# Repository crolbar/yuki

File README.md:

<h1 align="center">YUKI</h1>

<div align="center">
YUKI is a split diodless keyboard with a column stagger layout heavily inspired by <a href="https://github.com/diepala/cantor">cantor</a>.
</div>
<br/><br/>

Made with [Keyberon](https://github.com/TeXitoi/keyberon)

<br/>

### Layers
| Layer                                                                                      | Description              |
|--------------------------------------------------------------------------------------------|--------------------------|
| [Layer 0](https://www.keyboard-layout-editor.com/#/gists/67aaf9d778e9b2ddf6e25b263cbe5ed5) | Firmware Dvorak          |
| [Layer 1](https://www.keyboard-layout-editor.com/#/gists/5f7a4db98ea4d0b959304c4fe80d1d7f) | Numbers & Symbols        |
| [Layer 2](https://www.keyboard-layout-editor.com/#/gists/3af9d73abaec154f56b99b5a6c55cf5e) | Less used keys & Macros  |
| [Layer 3](https://www.keyboard-layout-editor.com/#/gists/ff861bef767ebb767786974deb496a8b) | Mouse movement & buttons |
| [Layer 4](https://www.keyboard-layout-editor.com/#/gists/a4c8d92eb2a6d883765b2eac82c46641) | Qwerty                   |

<br/>

### Features

- 44 keys, v0.1 - Cherry MX & v0.2 - Kailh Choc V1 switches
- Uses only 1U keycaps
- TRRS connection is used for communication between the two halves
- 2 USB-C connectors, with a choice from which the keyboard should send keystrokes
- Mouse control
- OLED display (not installed in the v0.2 picture)

<br/>

# Bill of Materials

| Product       | Qty | Note                                                                                                                                                                                                        |
|---------------|-----|-------------------------------------------------------------------------------------------------------------------------------------------------------------------------------------------------------------|
| YUKI PCB      | 2   | [KiCad](https://kicad.org/) project files can be found in `yuki_pcb` directory. I ordered them from [JLCPCB](https://jlcpcb.com). They are reversible so you will use the same pcb for both left and right. |
| STM32F401CCU6 | 2   | Can be found on aliexpress. I have ordered mine from a local vendor.                                                                                                                                        |
| TRRS jacks    | 2   | `PJ-320A`                                                                                                                                                                                                   |
| TRRS cable    | 1   | 3.5mm jack cable, with 3 stripes.                                                                                                                                                                           |
| Switches      | 44  | Cherry MX for v0.1 and Kailh Choc V1 for v0.2. Ordered from [splitkb](https://splitkb.com/collections/switches-and-keycaps/products/kailh-low-profile-choc-switches)                                        |
| Keycaps       | 44  | 1U keycaps. Ordered from [splitkb](https://splitkb.com/collections/switches-and-keycaps/products/blank-mbk-choc-low-profile-keycaps).                                                                       |

# Flashing the firmware

You will need rust installed so:
```
curl --proto '=https' --tlsv1.2 -sSf https://sh.rustup.rs | sh
```

cargo-binutils for stripping unused data from the rust binary and other optimizations:
```
rustup component add llvm-tools
cargo install cargo-binutils
```

dfu-util for flashing:
```
sudo pacman -S dfu-util
```

add the rust target for the MCU:
```
rustup target add thumbv7em-none-eabihf
```

then to compile the firmware:
``` 
cargo objcopy --bin yuki --release -- -O binary yuki.bin
```
for the right board add `--features right`

to flash enter dfu by holding BOOT clicking RESET and releasing BOOT and enter (can be tricky):
```
dfu-util -d 0483:df11 -a 0 --dfuse-address 0x08000000:leave -D yuki.bin"
```

After that to enter dfu just hold button 05 and 33 click reset and release the buttons.

### Nix

if you are on NixOS you could use the devShell:

enter the dev shell:
```
nix develop
```

and use the flash script that can be found in `flash.nix`
```
flash right
```

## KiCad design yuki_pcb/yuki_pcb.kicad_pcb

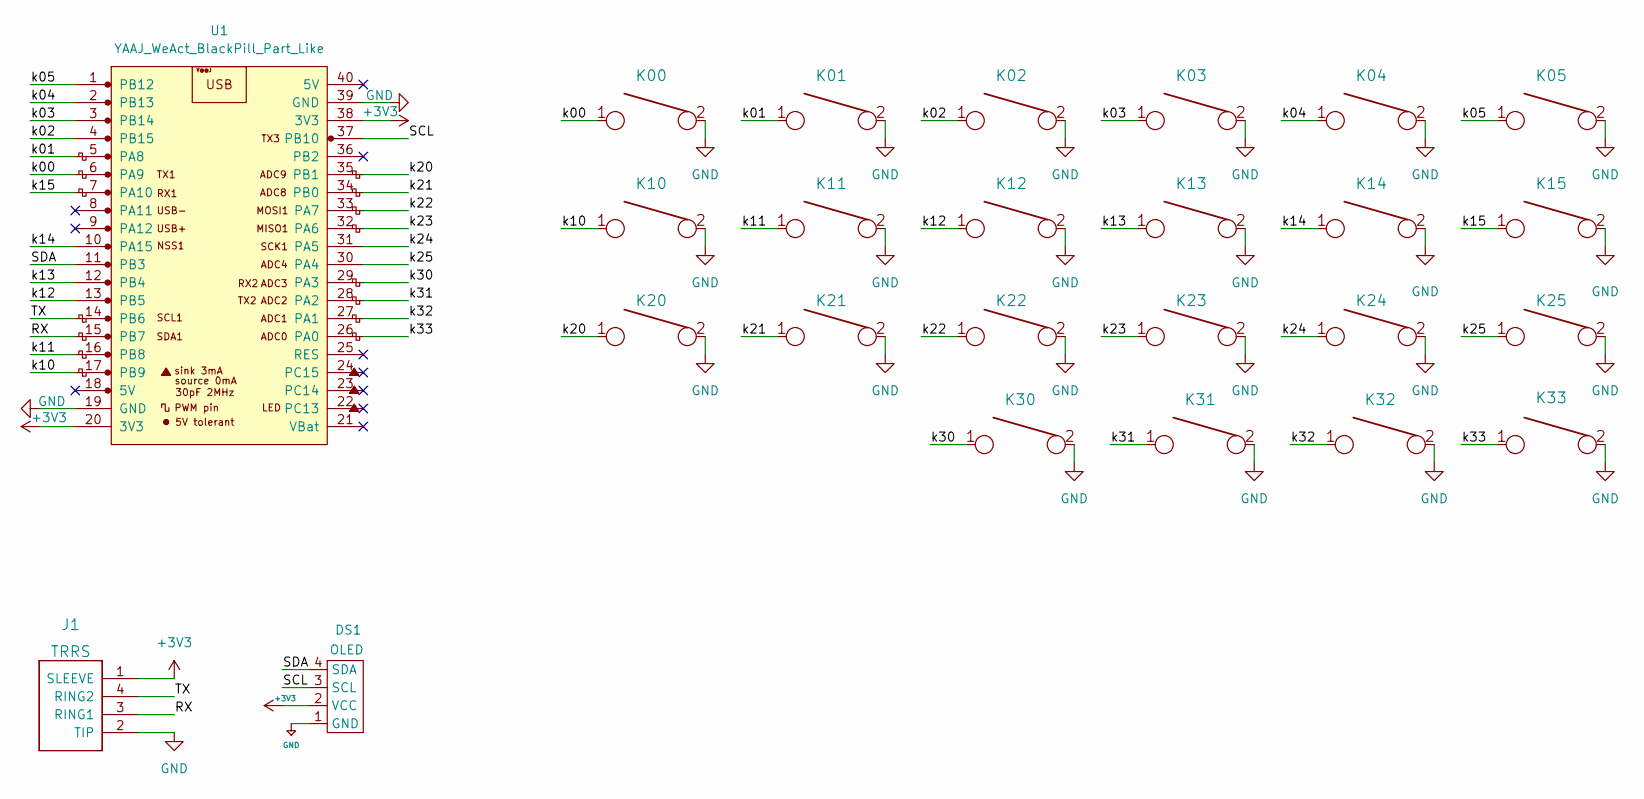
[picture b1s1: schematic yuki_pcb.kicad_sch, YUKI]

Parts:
DS1: OLED
J1: TRRS; MJ-4PP-9_Cantor_MX_TX-RX_Crossover
K00, K01, K02, K03, K04, K05, K10, K11, K12, K13, K14, K15, K20, K21, K22, K23, K24, K25, K30, K31, K32, K33: KEYSW; Kailh_Choc_PG1350_rev
U1: YAAJ_WeAct_BlackPill_Part_Like; YUKI_YAAJ_WeAct_BlackPill_2

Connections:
+3V3: DS1.2 (VCC), J1.1 (SLEEVE), U1.20 (3V3), U1.38 (3V3)
/RX: J1.3 (RING1), U1.15 (PB7)
/SCL: DS1.3 (SCL), U1.37 (PB10)
/SDA: DS1.4 (SDA), U1.11 (PB3)
/TX: J1.4 (RING2), U1.14 (PB6)
/k00: K00.1, U1.6 (PA9)
/k01: K01.1, U1.5 (PA8)
/k02: K02.1, U1.4 (PB15)
/k03: K03.1, U1.3 (PB14)
/k04: K04.1, U1.2 (PB13)
/k05: K05.1, U1.1 (PB12)
/k10: K10.1, U1.17 (PB9)
/k11: K11.1, U1.16 (PB8)
/k12: K12.1, U1.13 (PB5)
/k13: K13.1, U1.12 (PB4)
/k14: K14.1, U1.10 (PA15)
/k15: K15.1, U1.7 (PA10)
/k20: K20.1, U1.35 (PB1)
/k21: K21.1, U1.34 (PB0)
/k22: K22.1, U1.33 (PA7)
/k23: K23.1, U1.32 (PA6)
/k24: K24.1, U1.31 (PA5)
/k25: K25.1, U1.30 (PA4)
/k30: K30.1, U1.29 (PA3)
/k31: K31.1, U1.28 (PA2)
/k32: K32.1, U1.27 (PA1)
/k33: K33.1, U1.26 (PA0)
GND: DS1.1 (GND), J1.2 (TIP), K00.2, K01.2, K02.2, K03.2, K04.2, K05.2, K10.2, K11.2, K12.2, K13.2, K14.2, K15.2, K20.2, K21.2, K22.2, K23.2, K24.2, K25.2, K30.2, K31.2, K32.2, K33.2, U1.19 (GND), U1.39 (GND)

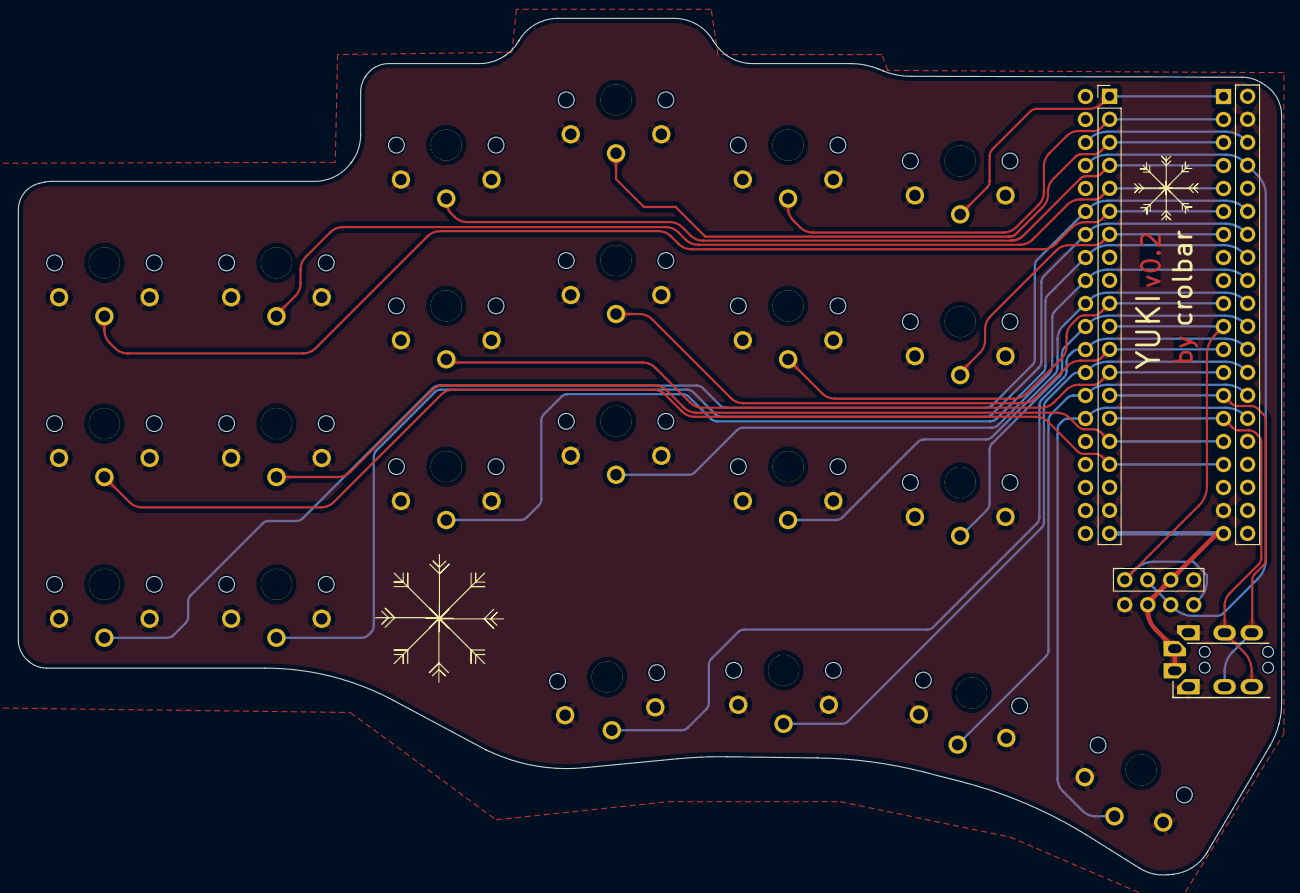
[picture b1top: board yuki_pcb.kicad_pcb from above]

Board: 2 copper layers, 139.5 x 94.6 mm, 25 parts (0 on the bottom side), 28 nets.

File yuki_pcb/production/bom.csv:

Designator,Footprint,Quantity,Value,LCSC Part #
DS1,OLED,1,OLED,
J1,MJ-4PP-9_Cantor_MX_TX-RX_Crossover,1,TRRS,
"K00, K01, K02, K03, K04, K05, K10, K11, K12, K13, K14, K15, K20, K21, K22, K23, K24, K25, K30, K31, K32, K33",CherryMX_rev,22,KEYSW,
U1,YUKI_YAAJ_WeAct_BlackPill_2,1,YAAJ_WeAct_BlackPill_Part_Like,

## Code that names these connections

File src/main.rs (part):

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        let gpioc = ctx.device.GPIOC.split();

        // easier dfu enter keys
        let pa0 = gpioa.pa0.into_pull_up_input();
        let pb12 = gpiob.pb12.into_pull_up_input();

        let mut timer = ctx.device.TIM2.counter_hz(&mut clocks);
        timer.start(1.kHz()).unwrap();
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
        // easier dfu check if keys are pressed
        // do this a bit after setting the pins to high
        let enter_dfu = pa0.is_low() && pb12.is_low();

        let matrix = interrupt::free(move |_| {
            DirectPinMatrix::new([
                [
                    Some(gpioa.pa9.into_pull_up_input().erase()),
                    Some(gpioa.pa8.into_pull_up_input().erase()),
                    Some(gpiob.pb15.into_pull_up_input().erase()),
                    Some(gpiob.pb14.into_pull_up_input().erase()),
                    Some(gpiob.pb13.into_pull_up_input().erase()),
                    Some(pb12.into_pull_up_input().erase()),
                ],
                [
                    Some(gpiob.pb9.into_pull_up_input().erase()),
                    Some(gpiob.pb8.into_pull_up_input().erase()),
                    Some(gpiob.pb5.into_pull_up_input().erase()),
                    Some(gpiob.pb4.into_pull_up_input().erase()),
                    Some(gpioa.pa15.into_pull_up_input().erase()),
                    Some(gpioa.pa10.into_pull_up_input().erase()),
                ],
                [
                    Some(gpiob.pb1.into_pull_up_input().erase()),
                    Some(gpiob.pb0.into_pull_up_input().erase()),
                    Some(gpioa.pa7.into_pull_up_input().erase()),
                    Some(gpioa.pa6.into_pull_up_input().erase()),
                    Some(gpioa.pa5.into_pull_up_input().erase()),
                    Some(gpioa.pa4.into_pull_up_input().erase()),
                ],
                [
                    None,
                    None,
                    Some(gpioa.pa3.into_pull_up_input().erase()),
                    Some(gpioa.pa2.into_pull_up_input().erase()),
                    Some(gpioa.pa1.into_pull_up_input().erase()),
                    Some(pa0.into_pull_up_input().erase()),
                ],
            ]).unwrap()
        });
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        let mut serial = serial::Serial::new(
            ctx.device.USART1,
            interrupt::free(move |_| 
                (gpiob.pb6.into_alternate::<7>(), gpiob.pb7.into_alternate::<7>())
            ),
            38_400.bps(),
            &mut clocks
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                use_right_usb: USE_RIGHT_USB_INIT,
                #[cfg(feature = "oled")]
                oled: OLED::new(
                    gpiob.pb10.into_alternate().set_open_drain(),
                    gpiob.pb3.into_alternate().set_open_drain(),
                    ctx.device.I2C2, &clocks
                )
            },
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
    #[idle(local = [enter_dfu])]
    fn idle(ctx: idle::Context) -> ! {
        // if pa0 && pb12 are shorted and the board resets this will load dfu
        if *ctx.local.enter_dfu {
            unsafe { cortex_m::asm::bootload(0x1FFF0000 as _) }
        }
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
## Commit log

2024-04-07 init
2024-04-07 rounded edges
2024-04-07 more silksreen
2024-04-21 some firmware
2024-04-24 serial comms and easier dfu entering
2024-04-25 layers!
2024-04-25 capslock led
2024-04-25 display curr_layer on OLED
2024-04-29 README: column stagger instead of ortholinier
2024-04-29 flake file for nix dev shell
2024-04-29 add button to change which board sends keyboard reports
2024-04-30 fix crash when trying to write kb_report when usb not connected
2024-04-30 revome unsafe blocks && some refactor
2024-05-03 remove toggle layer 2 (unused)
2024-05-05 add layer 2 as condition on usb switcher
2024-05-15 Create LICENSE
2024-05-23 trying out shift on BS key
2024-05-24 move BS in l2 && dedicated shift key
2024-05-24 bit of refactor && idle func
2024-05-25 one byte comms?
2024-05-26 a mouse in the keyboard?
2024-05-28 scuffy img in the keyboard?
2024-05-28 oled: forgot to init the display
2024-05-28 fix: windows no likey mouse in the keyboard
2024-05-29 scuffy mouse speedup
2024-05-29 add shtuff to README
2024-06-27 swap alt and ctrl && more media buttons
2024-06-27 change mouse speedup to hold
2024-07-01 sketch slower scrolling
2024-08-19 config > config.toml
2024-08-19 update nix flake
2025-03-15 choc footprint + half tracks done
2025-03-15 back tracks done
2025-03-15 pcb: edge cuts
2025-03-16 v0.2
2025-03-23 extract constant values into consts
2025-03-23 feat: oled feature + nix flash script
2025-03-25 layout(qwerty): change grave->tab & Meta->Ctrl
2025-03-25 v0.2 image & update readme
2025-03-25 add names & year in license
2025-03-25 v0.2 with Choc switches!
2025-03-27 fix: dfu on keyboard plug in. (check for dfu enter a bit later)
2025-11-07 feat(layout): LAYER4 toggle in LAYER3 left side
2025-11-07 refac(layout): more readable layouts
2025-12-10 README: add layer 3 & 4 layouts
2026-02-05 Bump time from 0.3.36 to 0.3.47
    Bumps [time](https://github.com/time-rs/time) from 0.3.36 to 0.3.47.
    - [Release notes](https://github.com/time-rs/time/releases)
    - [Changelog](https://github.com/time-rs/time/blob/main/CHANGELOG.md)
    - [Commits](https://github.com/time-rs/time/compare/v0.3.36...v0.3.47)
    ---
    updated-dependencies:
